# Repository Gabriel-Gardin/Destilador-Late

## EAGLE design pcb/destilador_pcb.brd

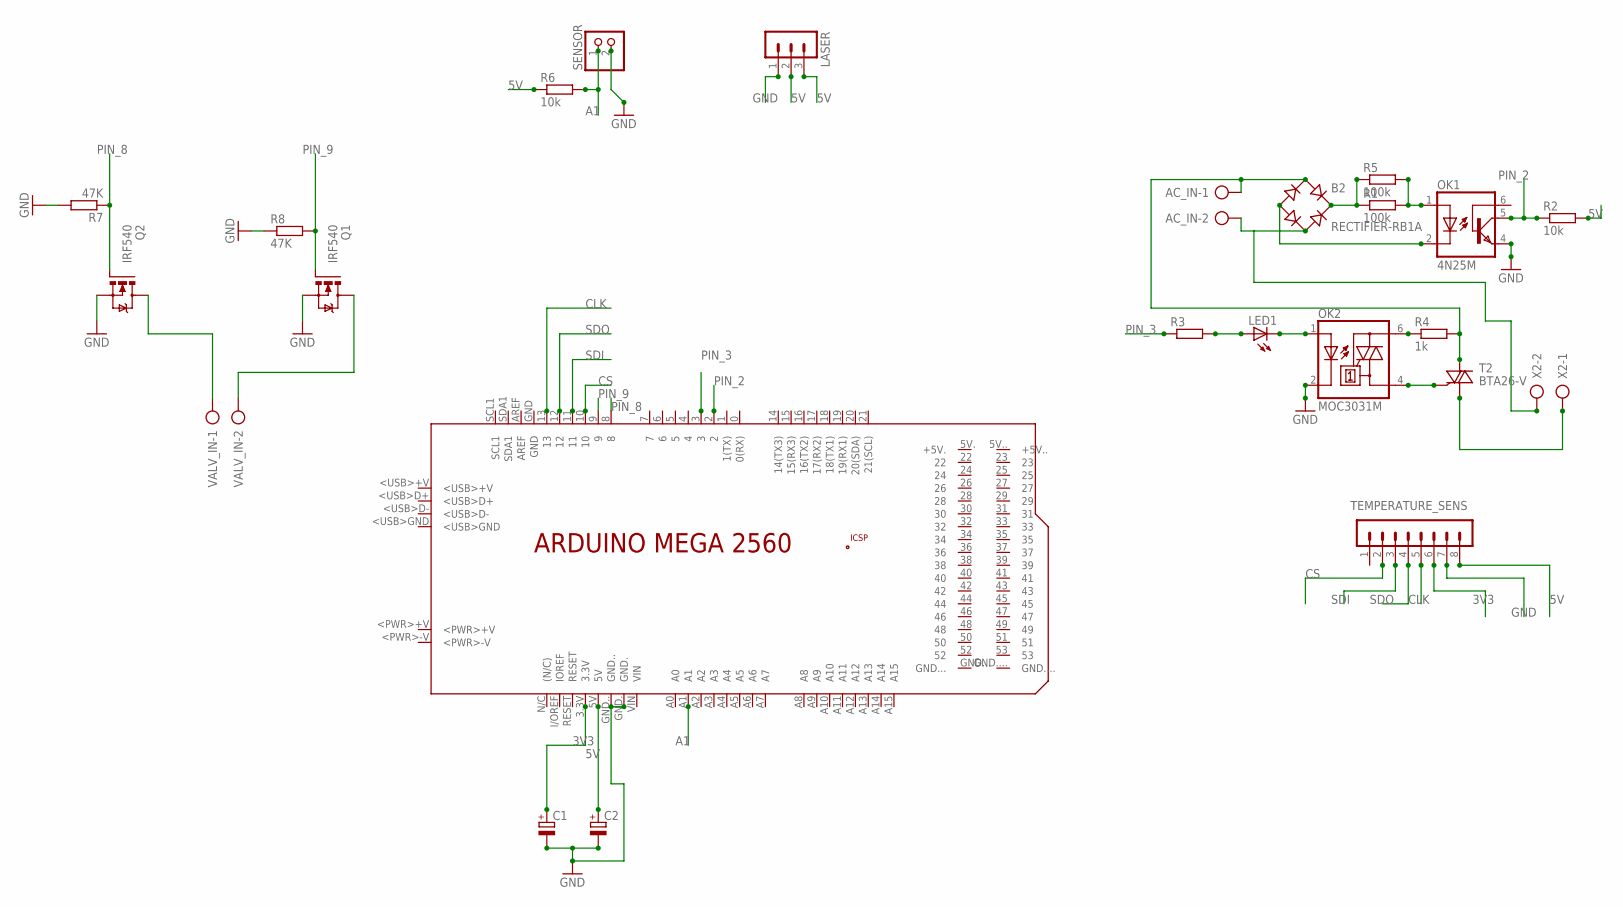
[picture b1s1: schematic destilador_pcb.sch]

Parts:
AC_IN: AK300/2
B2: RECTIFIER-RB1A; RB1A
C1, C2: CPOL-EUE2,5-6E; E2,5-6E
LASER: MA03-1
LED1: LED5MM
OK1: 4N25M; DIL06
OK2: MOC3031M; DIL06
PCB1: ARDUINO_MEGA2560
Q1, Q2: IRF540; TO220BV
R1, R5: 100k; 0207/7
R2, R6: 10k; 0207/7
R3: R-EU_0207/7; 0207/7
R4: 1k; 0207/7
R7, R8: 47K; 0207/7
SENSOR: PINHD-1X2; 1X02
T2: BTA26-V; TOP3S-1
TEMPERATURE_SENS: MA08-1
VALV_IN: AK500/2-H
X2: AK300/2

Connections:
3V3: C1.+, PCB1.3.3V, TEMPERATURE_SENS.6
5V: C2.+, LASER.2, LASER.3, PCB1.5V, R2.2, R6.1, TEMPERATURE_SENS.8
A1: PCB1.A1, R6.2, SENSOR.1
CLK: PCB1.13, TEMPERATURE_SENS.5
CS: PCB1.10, TEMPERATURE_SENS.2
GND: C1.-, C2.-, LASER.1, OK1.4 (EMI), OK2.2 (C), PCB1.GND., PCB1.GND.., Q1.S, Q2.S, R7.2, R8.1, SENSOR.2, TEMPERATURE_SENS.7
unnamed: AC_IN.1, B2.AC1, R4.2, T2.A2
unnamed: AC_IN.2, B2.AC2, X2.2
unnamed: B2.-, OK1.2 (C)
unnamed: B2.+, R1.1, R5.1
unnamed: OK1.1 (A), R1.2, R5.2
unnamed: LED1.A, R3.2
unnamed: OK2.4 (A1), T2.G
unnamed: OK2.6 (A2), R4.1
unnamed: LED1.K (C), OK2.1 (A)
unnamed: T2.A1, X2.1
unnamed: Q2.D, VALV_IN.1
unnamed: Q1.D, VALV_IN.2
PIN_2: OK1.5 (COL), PCB1.2, R2.1
PIN_3: PCB1.3, R3.1
PIN_8: PCB1.8, Q2.G, R7.1
PIN_9: PCB1.9, Q1.G, R8.2
SDI: PCB1.11, TEMPERATURE_SENS.3
SDO: PCB1.12, TEMPERATURE_SENS.4

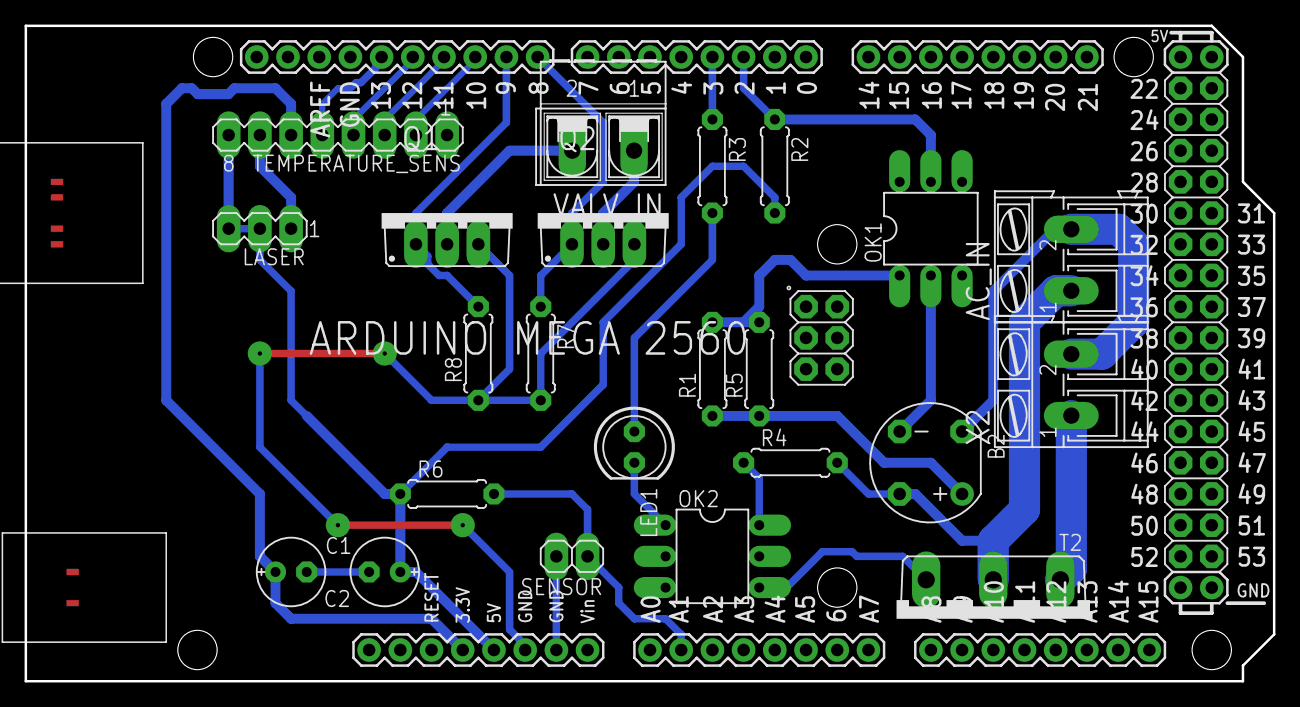
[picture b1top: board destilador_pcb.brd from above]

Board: 2 copper layers, 101.6 x 53.3 mm, 24 parts (0 on the bottom side), 24 nets.

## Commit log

2019-01-27 Add files via upload
    Commit inicial do projeto do destilador
2019-01-27 Commit que removeu os arquivos temporários da PCB
2019-01-28 Adicionei o .gitignore
2019-01-28 Adicionando PCB
2019-01-28 PCB finalizada
2019-02-01 Pequenas alteraçoes no sketch arduino
2019-02-05 Atualizações no código
2019-02-06 Software identifica a porta serial automaticamente
2019-02-06 Corrigi bug da serial e adicionei text status para a temperatura
2019-02-08 GUI mostrando a temperatura corretamente
2019-02-11 Versão provisória apenas para qualificaçao da bruna
2019-02-11 Função #0ff zera totalemtne a potencia
2019-05-29 Add nirserial
